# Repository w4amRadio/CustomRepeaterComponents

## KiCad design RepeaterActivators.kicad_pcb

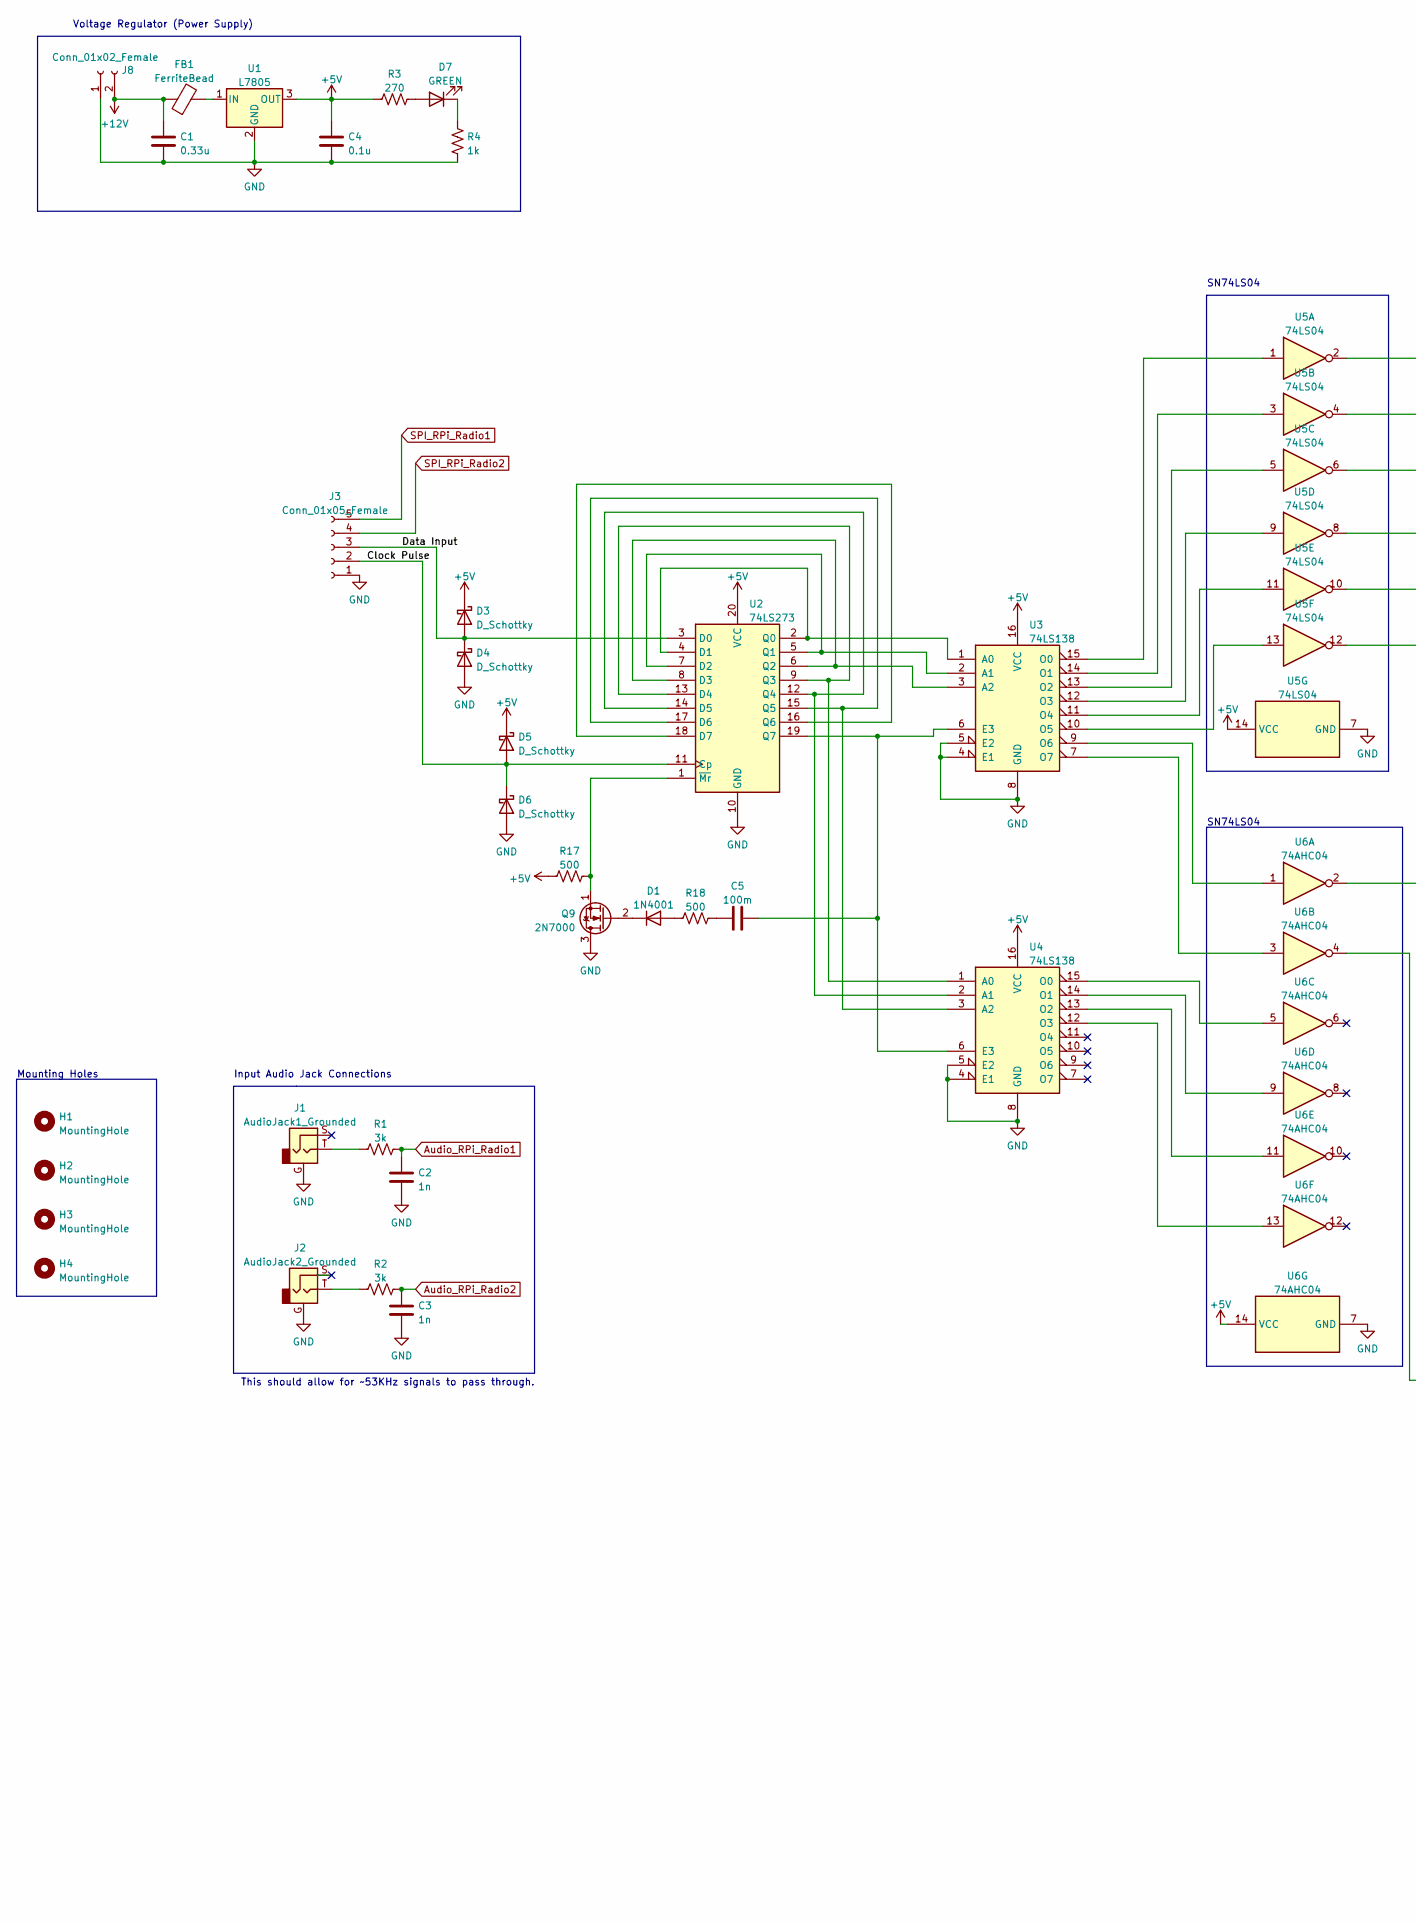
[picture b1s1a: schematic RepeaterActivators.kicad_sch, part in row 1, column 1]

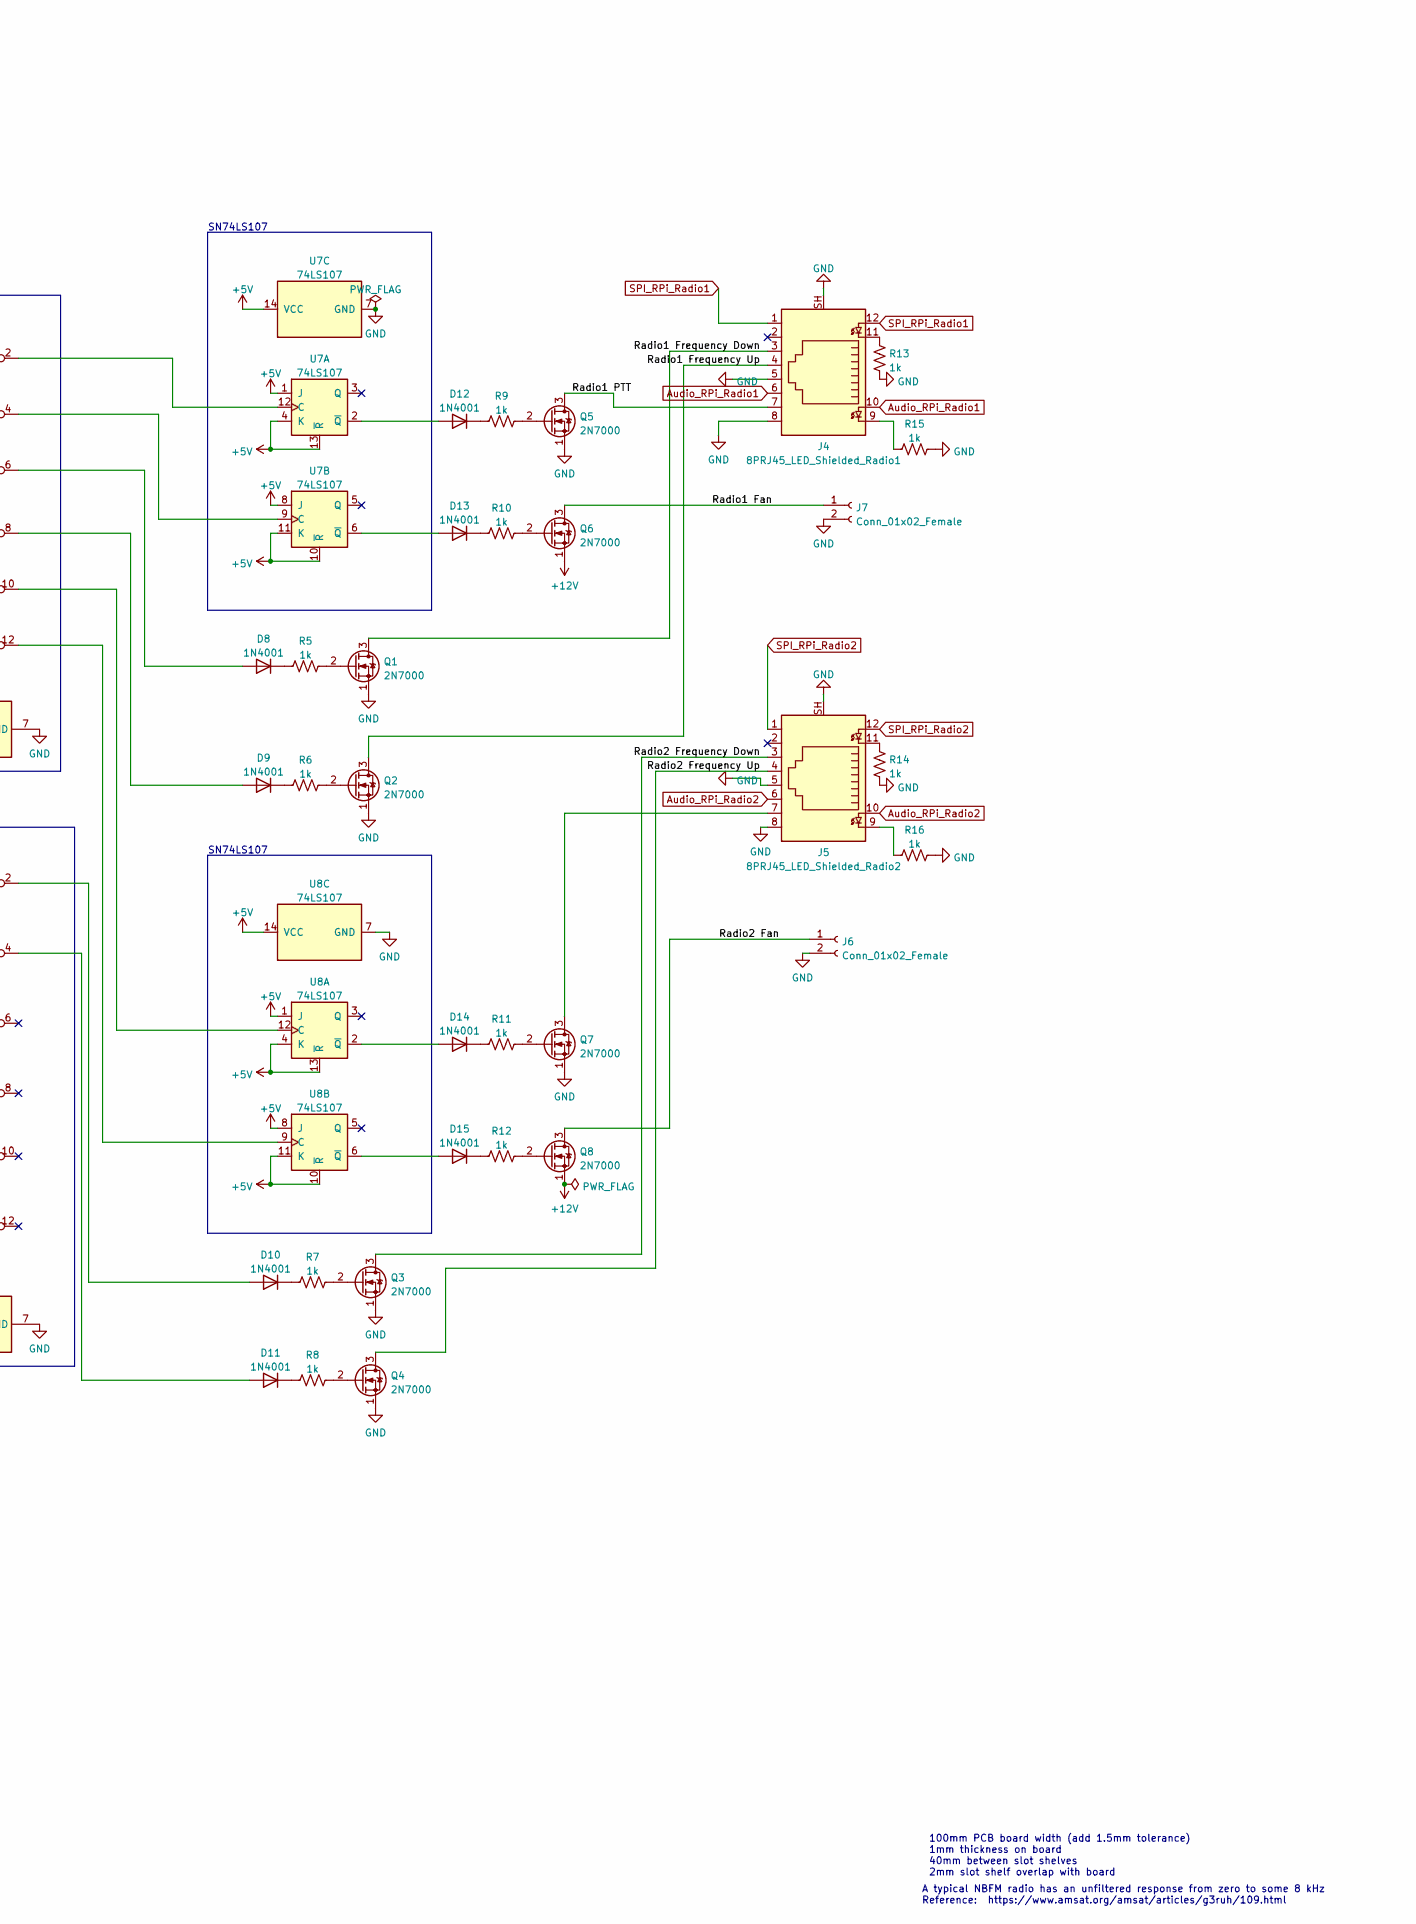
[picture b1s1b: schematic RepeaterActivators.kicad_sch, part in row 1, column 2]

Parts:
C1: 0.33u; C_Disc_D3.4mm_W2.1mm_P2.50mm
C2, C3: 1n; C_Disc_D3.4mm_W2.1mm_P2.50mm
C4: 0.1u; C_Disc_D3.4mm_W2.1mm_P2.50mm
C5: 100m; C_Disc_D3.4mm_W2.1mm_P2.50mm
D1, D8, D9, D10, D11, D12, D13, D14, D15: 1N4001; D_DO-41_SOD81_P10.16mm_Horizontal
D3, D4, D5, D6: D_Schottky; D_5W_P12.70mm_Horizontal
D7: GREEN; LED_D3.0mm
FB1: FerriteBead; L_0603_1608Metric
H1, H2, H3, H4: MountingHole; MountingHole_2.7mm_M2.5
J1: AudioJack1_Grounded; Jack_3.5mm_CUI_SJ-3523-SMT_Horizontal
J2: AudioJack2_Grounded; Jack_3.5mm_CUI_SJ-3523-SMT_Horizontal
J3: Conn_01x05_Female; PinSocket_1x05_P2.00mm_Horizontal
J4: 8PRJ45_LED_Shielded_Radio1; RJ45_Amphenol_RJHSE538X
J5: 8PRJ45_LED_Shielded_Radio2; RJ45_Amphenol_RJHSE538X
J6, J7, J8: Conn_01x02_Female; PinSocket_1x02_P2.00mm_Horizontal
Q1, Q2, Q3, Q4, Q5, Q6, Q7, Q8, Q9: 2N7000; TO-92_Inline
R1, R2: 3k; R_Axial_DIN0207_L6.3mm_D2.5mm_P7.62mm_Horizontal
R3: 270; R_Axial_DIN0207_L6.3mm_D2.5mm_P7.62mm_Horizontal
R4, R5, R6, R7, R8, R9, R10, R11, R12, R13, R14, R15, R16: 1k; R_Axial_DIN0207_L6.3mm_D2.5mm_P7.62mm_Horizontal
R17, R18: 500; R_Axial_DIN0207_L6.3mm_D2.5mm_P7.62mm_Horizontal
U1: L7805; TO-220-3_Vertical
U2: 74LS273; DIP-20_W7.62mm
U3, U4: 74LS138; DIP-16_W7.62mm
U5: 74LS04; DIP-14_W7.62mm
U6: 74AHC04; DIP-14_W7.62mm
U7, U8: 74LS107; DIP-14_W7.62mm

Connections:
+5V: C4.1, D3.1 (K), D5.1 (K), R3.1, R17.1, U1.3 (OUT), U2.20 (VCC), U3.16 (VCC), U4.16 (VCC), U5.14 (VCC), U6.14 (VCC), U7.1 (J), U7.4 (K), U7.8 (J), U7.10 (~R), U7.11 (K), U7.13 (~R), U7.14 (VCC), U8.1 (J), U8.4 (K), U8.8 (J), U8.10 (~R), U8.11 (K), U8.13 (~R), U8.14 (VCC)
+12V: C1.1, FB1.1, J8.2, Q6.1 (S), Q8.1 (S)
/Clock Pulse: D5.2 (A), D6.1 (K), J3.2, U2.11 (Cp)
/Data Input: D3.2 (A), D4.1 (K), J3.3, U2.3 (D0)
/Radio1 Fan: J7.1, Q6.3 (D)
/Radio1 Frequency Down: J4.3, Q1.3 (D)
/Radio1 Frequency Up: J4.4, Q2.3 (D)
/Radio1 PTT: J4.7, Q5.3 (D)
/Radio2 Fan: J6.1, Q8.3 (D)
/Radio2 Frequency Down: J5.3, Q3.3 (D)
/Radio2 Frequency Up: J5.4, Q4.3 (D)
Audio_RPi_Radio1: C2.1, J4.6, J4.10, R1.2
Audio_RPi_Radio2: C3.1, J5.6, J5.10, R2.2
GND: C1.2, C2.2, C3.2, C4.2, D4.2 (A), D6.2 (A), J1.G, J2.G, J3.1, J4.5, J4.8, J4.SH, J5.5, J5.8, J5.SH, J6.2, J7.2, J8.1, Q1.1 (S), Q2.1 (S), Q3.1 (S), Q4.1 (S), Q5.1 (S), Q7.1 (S), Q9.3 (D), R4.2, R13.2, R14.2, R15.1, R16.1, U1.2 (GND), U2.10 (GND), U3.4 (E1), U3.5 (E2), U3.8 (GND), U4.4 (E1), U4.5 (E2), U4.8 (GND), U5.7 (GND), U6.7 (GND), U7.7 (GND), U8.7 (GND)
unnamed: C5.1, R18.2
unnamed: D1.1 (K), Q9.2 (G)
unnamed: D1.2 (A), R18.1
unnamed: D7.1 (K), R4.1
unnamed: D7.2 (A), R3.2
unnamed: D8.1 (K), R5.1
unnamed: D8.2 (A), U5.6
unnamed: D9.1 (K), R6.1
unnamed: D9.2 (A), U5.8
unnamed: D10.1 (K), R7.1
unnamed: D10.2 (A), U6.2
unnamed: D11.1 (K), R8.1
unnamed: D11.2 (A), U6.4
unnamed: D12.1 (K), R9.1
unnamed: D12.2 (A), U7.2 (~Q)
unnamed: D13.1 (K), R10.1
unnamed: D13.2 (A), U7.6 (~Q)
unnamed: D14.1 (K), R11.1
unnamed: D14.2 (A), U8.2 (~Q)
unnamed: D15.1 (K), R12.1
unnamed: D15.2 (A), U8.6 (~Q)
unnamed: FB1.2, U1.1 (IN)
unnamed: J1.T, R1.1
unnamed: J2.T, R2.1
unnamed: J4.9, R15.2
unnamed: J4.11, R13.1
unnamed: J5.7, Q7.3 (D)
unnamed: J5.9, R16.2
unnamed: J5.11, R14.1
unnamed: Q1.2 (G), R5.2
unnamed: Q2.2 (G), R6.2
unnamed: Q3.2 (G), R7.2
unnamed: Q4.2 (G), R8.2
unnamed: Q5.2 (G), R9.2
unnamed: Q6.2 (G), R10.2
unnamed: Q7.2 (G), R11.2
unnamed: Q8.2 (G), R12.2
unnamed: Q9.1 (S), R17.2, U2.1 (~Mr)
unnamed: U2.2 (Q0), U2.4 (D1), U3.1 (A0)
unnamed: U2.5 (Q1), U2.7 (D2), U3.2 (A1)
unnamed: U2.6 (Q2), U2.8 (D3), U3.3 (A2)
unnamed: U2.12 (Q4), U2.14 (D5), U4.2 (A1)
unnamed: U2.9 (Q3), U2.13 (D4), U4.1 (A0)
unnamed: U2.15 (Q5), U2.17 (D6), U4.3 (A2)
unnamed: U2.16 (Q6), U2.18 (D7)
unnamed: U3.7 (O7), U6.3
unnamed: U3.9 (O6), U6.1
unnamed: U3.10 (O5), U5.13
unnamed: U3.11 (O4), U5.11
unnamed: U3.12 (O3), U5.9
unnamed: U3.13 (O2), U5.5
unnamed: U3.14 (O1), U5.3
unnamed: U3.15 (O0), U5.1
unnamed: C5.2, U2.19 (Q7), U3.6 (E3), U4.6 (E3)
unnamed: U4.12 (O3), U6.13
unnamed: U4.13 (O2), U6.11
unnamed: U4.14 (O1), U6.9
unnamed: U4.15 (O0), U6.5
unnamed: U5.2, U7.12 (C)
unnamed: U5.4, U7.9 (C)
unnamed: U5.10, U8.12 (C)
unnamed: U5.12, U8.9 (C)
SPI_RPi_Radio1: J3.5, J4.1, J4.12
SPI_RPi_Radio2: J3.4, J5.1, J5.12

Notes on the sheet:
SN74LS04
Input Audio Jack Connections
100mm PCB board width (add 1.5mm tolerance) 1mm thickness on board 40mm between slot shelves 2mm slot shelf overlap with board
SN74LS107
Voltage Regulator (Power Supply)
Mounting Holes
This should allow for ~53KHz signals to pass through.
A typical NBFM radio has an unfiltered response from zero to some 8 kHz Reference: https://www.amsat.org/amsat/articles/g3ruh/109.html

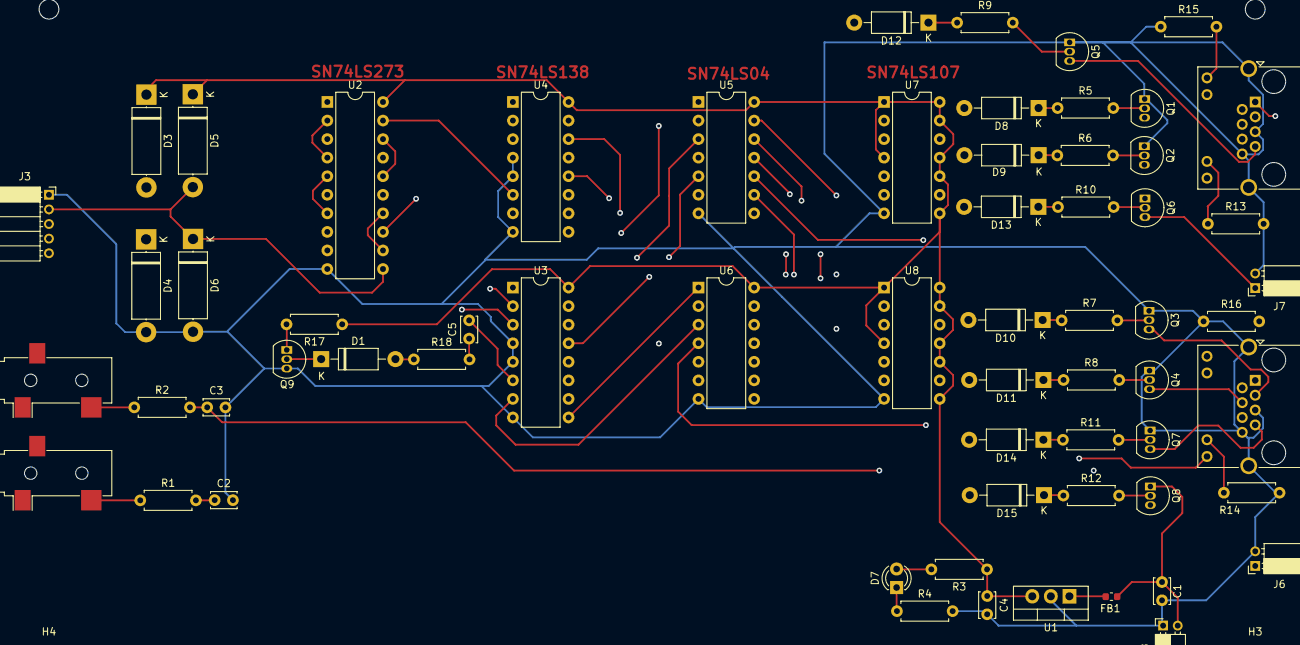
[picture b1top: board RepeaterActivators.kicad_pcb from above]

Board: 4 copper layers, 67 parts (0 on the bottom side), 78 nets.

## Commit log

2022-12-21 DBD: initial commit
2022-12-21 DBD: annoying main branch
2022-12-21 DBD: gitignore + error check fixes
2022-12-21 DBD: attempt at esd protection, probably look harder at this later
2022-12-23 DBD: added SN74LS107 JK Flip Flops for persistent activation of fans and ptt's until pi sends a code to de-activate
2022-12-23 DBD: changed rpi connector to 1x6, changing radio connectors to shielded rj-45 with led's
2022-12-23 DBD: converted connectors to rj-45 ethernet, added audio jack input for mic audio with low pass filter, added 2 2 pin connectors for radio fans
2022-12-23 DBD: v1.0 complete
2022-12-26 DBD: changed master reset switch so it's automatically toggled once msb is set
2022-12-26 DBD: positioning components on the board
2022-12-27 DBD: Routing complete sans minor errors
2022-12-27 DBD: fixed some silkscreen overlaps
2022-12-27 DBD: shrank board a bit
2022-12-27 DBD: Labelling
2023-01-21 DBD: Removed RC and added delayed start 555 IC for MR on 273 due to discoveries in breadboarding
2023-01-21 DBD: demux activation fix
